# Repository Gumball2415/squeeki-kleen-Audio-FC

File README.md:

# squeeki-kleen! Audio FC

an open-source hardware external preamp modboard for the NES and FamiCom

## About

A few months ago, I discovered the main source of noisy interference for the audio in the FamiCom, which is the hex inverter chip. The other signals passing through the hex inverter chip is the interference heard in the audio.

Therefore, to reduce the interference as much as possible, the APU pins and preamp circuit must be completely isolated from the hex inverter chip. This is where this modboard comes in.

Note that this KiCad project is optimized for JLCPCB manufacturing, so you may have to modify how the gerber files are generated, remove the part number silkscreen on the back, etc.

<div align="center">
	
</div>

## Installation

This demonstration uses the RF FamiCom motherboard, revision CPU-07. However, these requirements can be easily adapted to different consoles and motherboard revisions, such as the NES.

This demonstration also uses an earlier revision board, so the look may differ, but the instructions should remain the same.

Here is the full motherboard overview of what modifications need to be done:

<div align="center">

</div>

### Instructions

1. Isolate Pin 1 and 2 of the 2A03 by cutting their traces as shown:

<div align="center">
	
</div>

2. Short the input of the stock preamp circuit to ground (solder bridge violet, pins 14 and 15 of U7)

<div align="center">
	
</div>

3. Isolate the output of the stock preamp circuit and the old audio path (cut blue)
	- Cut the trace after the `SOU` test pad
	- Cut the trace of R7 before it goes to pin 13 of U7
	- Isolate the via near C11, which leads to pin 45 of the cartridge slot. This prevents the leftover trace leaving the `SOU` test pad acting as an antenna to unwanted interference near the bus traces.

<div align="center">

</div>

Once these are done, simply install the board underneath the 2A03, and connect the output pad to the appropriate output path.

### Connecting the output

When installed, it will look something similar to this:

<div align="center">

</div>

Note that this is a v0.9 prototype, where the output goes to the left. *The latest version's output goes to the right*.

Jump the output to pin 45 of the cartridge connector in order for the audio to be mixed with cartridge expansion audio as follows:

<div align="center">
	
</div>

## License

This is licensed under the [TAPR Open Hardware License](http://www.tapr.org/OHL).

Copyright Persune 2026.

## Credits

Special thanks to:

- The NESDev and MDFourier community for advice and help
- [@tianfeng33](https://github.com/tianfeng33) for help with the preamp circuit
- konakonaa for the squeeki-kleen! namesake
- [@Lockster-Inc](https://github.com/Lockster-Inc) for the FamiCom PCB scans

## Support

If you enjoy this project or find it helpful, please support me on [Ko-Fi](https://ko-fi.com/persune) or [Patreon](https://www.patreon.com/persune)!

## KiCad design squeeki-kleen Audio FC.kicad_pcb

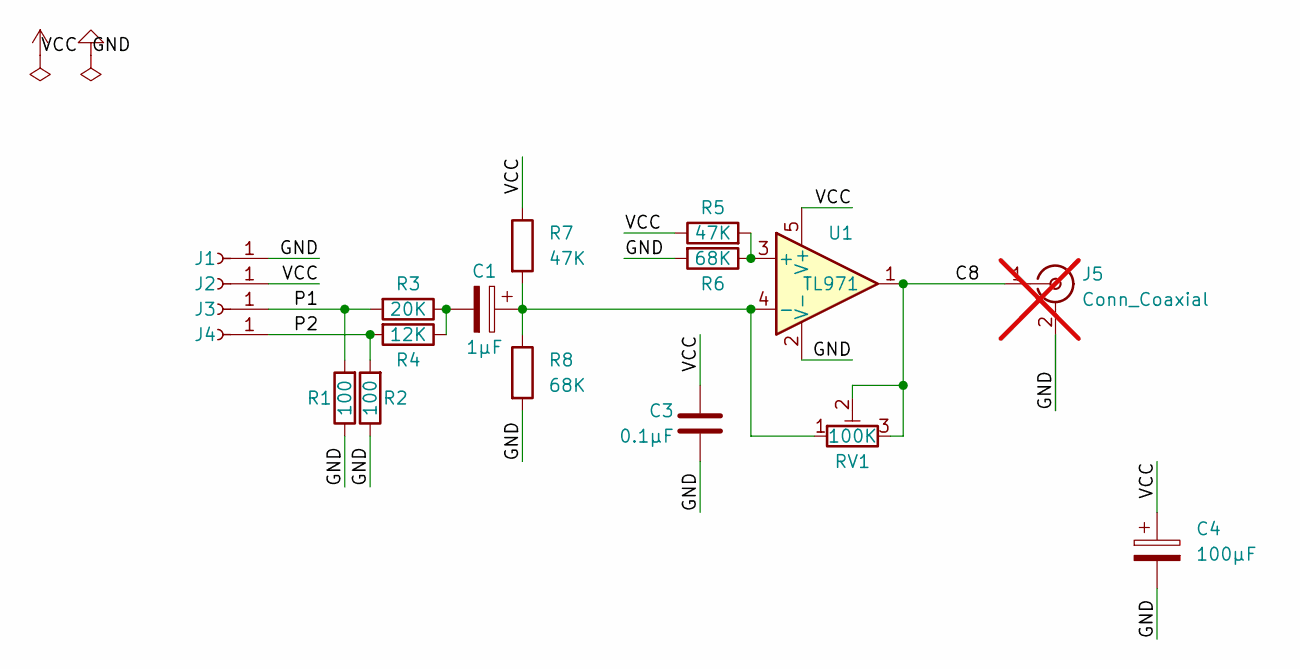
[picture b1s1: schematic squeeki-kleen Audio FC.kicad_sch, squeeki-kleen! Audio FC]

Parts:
C1: 1µF; CP_Elec_4x5.4
C3: 0.1µF; C_0805_2012Metric_Pad1.18x1.45mm_HandSolder
C4: 100µF; CP_Elec_6.3x4.5
J1: GND; Custom_THT
J2: VCC; Custom_THT
J3: P1; Custom_THT
J4: P2; Custom_THT
J5: Conn_Coaxial; MMCX_Molex_73415-0961_Horizontal_0.8mm-PCB; not fitted
R1, R2: 100; R_0805_2012Metric_Pad1.20x1.40mm_HandSolder
R3: 20K; R_0805_2012Metric_Pad1.20x1.40mm_HandSolder
R4: 12K; R_0805_2012Metric_Pad1.20x1.40mm_HandSolder; LCSC C316787
R5, R7: 47K; R_0805_2012Metric_Pad1.20x1.40mm_HandSolder
R6, R8: 68K; R_0805_2012Metric_Pad1.20x1.40mm_HandSolder
RV1: 100K; Potentiometer_Bourns_3224W_Vertical; LCSC C53229
U1: TL971; SOT-23-5

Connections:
/C8: J5.1 (In), RV1.2, RV1.3, U1.1
/P1: J3.1, R1.2, R3.2
/P2: J4.1, R2.2, R4.2
GND: C3.2, C4.2, J1.1, J5.2 (Ext), R1.1, R2.1, R6.2, R8.2, U1.2 (V-)
unnamed: C1.2, R3.1, R4.1
unnamed: R5.2, R6.1, U1.3 (+)
unnamed: C1.1, R7.2, R8.1, RV1.1, U1.4 (-)
VCC: C3.1, C4.1, J2.1, R5.1, R7.1, U1.5 (V+)

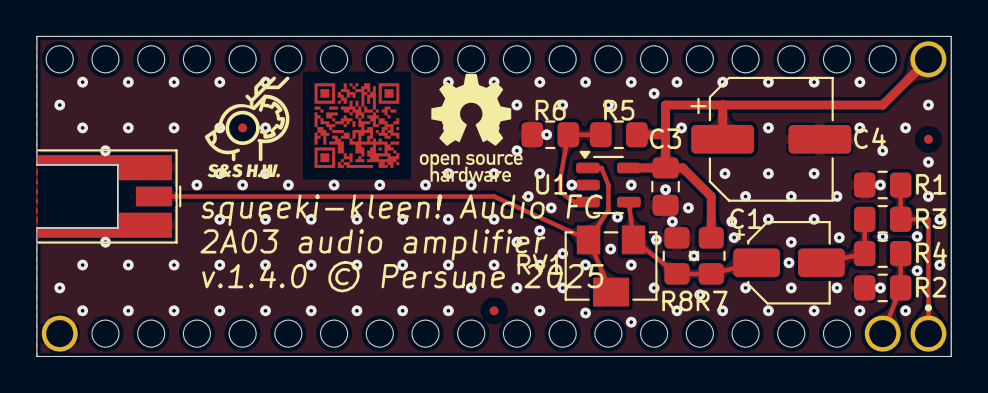
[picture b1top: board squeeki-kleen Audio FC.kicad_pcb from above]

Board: 2 copper layers, 50.8 x 17.7 mm, 21 parts (0 on the bottom side), 8 nets.

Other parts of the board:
Ref**: Val**; qr
svg2mod: G***; oshw-logo 6x6mm
svg2mod#2: G***; maustech icon fiducial 0-50mm 1-50mm

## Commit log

2021-09-04 Add readme and license
2021-09-04 Hotlink Github usernames
2021-10-21 Rev. 1.1.0
    - change edge cuts to be more panelization-friendly
    - use plated through holes instead of castellated holes
    - dagga art by https://twitter.com/pickleknotart
    - widen ground pad next to the audio out pad
2021-10-21 C3 capacitor filtering disclaimer
2021-10-23 Rev 1.2.0
    - change edge cuts to reduce unused space
    - add THT on pin 30 to add support
    - add labels on output pads
    - thanks to grievre for feedback
2022-04-23 KiCad 6.0
2022-04-23 ignore KiCad 6 backups
2022-04-23 Curvify traces
2022-04-23 Art by Pickleknot
2022-12-13 Adjust via size and copper fill
2022-12-13 Add teardrops, HTML BOM, and trace rounding
2022-12-13 Update PCB image
2022-12-13 Update version
2023-04-05 Add funding
2025-04-05 Update board layout, add level adjustment
2025-04-05 Update schematics
2026-06-29 docs: Update README.md

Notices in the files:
squeeki-kleen Audio FC.kicad_pcb:
v.1.4.0 © Persune 2025
